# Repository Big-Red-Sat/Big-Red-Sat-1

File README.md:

# Big Red Sat-1

## Introduction 

This repository contains the original designs for the Big Red Sat-1 1U CubeSat, conceived, designed, and launched by a multi-disciplinary team of middle schoolers and high schoolers from the Nebraska public school system, as well as undergraduate students and graduate students from the University of Nebraska-Lincoln.  

The goal of this scientific mission is to characterize the performance and degradation of experimental perovskite solar cells from the National Renewable Energy Laboratory while in low earth orbit.  To accomplish this, a custom precision curve tracer was designed along with a low-Ohm analog multiplexer that was integrated with Near Space Launch's 1U FastBus CubeSat Platform, which incorporates an electrical power system and Iridium satellite communication system for telemetry.  

Electrical connections to the perovskite solar cell samples were made using pogo-pins, with the temperature of each sample being collected with a high-precision temperature sensor affixed to their back face with EP30-2 epoxy.  The enclosure was designed to be airtight to prevent degradation due to humidity and oxygen, so a pressure and humidity sensor were included to monitor changes in this performance.  Since the final samples had a coverslip epoxied to protect the perovskite layer, the airtight property was considered a redundancy.

Big Red Sat-1 was integrated into the Nanoracks CubeSat Deployer 27 (NRCSD27) on 12 December 2023 and launched on 21 March 2024 on the SpaceX CRS-30 mission.   

Big Red Sat-1 was deployed from NRCSD27 by Voyager Space on 18 April 2024 at 18:05:09 UTC ([Deployment Clip](https://www.youtube.com/clip/UgkxD5o3cp39FE0SL8AzyLTBCwdvlqdmNVEa)).  The satellite made first communication with the operations team at 03:00:10 UTC on 19 April 2024.  The satellite deorbited sometime after 23:41:51 UTC on 1 August 2024 after 105 days of operation.

## TLE Data

[Up to date TLE data and visualizations](https://orbit.ing-now.com/satellite/59560/1998-067wk/1998-067wk/)

## Launch Patch

Original concept by Morgan Hurtz, branding by Vince Orsi.

## Current Satellite Location

[SatNOGS DB - Big Red Sat-1](https://db.satnogs.org/satellite/YJQI-7143-2488-2930-9322#mapcontent)

## Prototyping Designs

- [Prototype curve tracers for high altitude balloons](https://github.com/wsarce/Big-Red-Sat-1/tree/main/Prototyping/SIV_pcb)
- [Prototype digital potentiometer curve tracer](https://github.com/wsarce/Big-Red-Sat-1/tree/main/Prototyping/singular_SIV)
- [Prototype resistor ladder curve tracer in LaunchPad form factor](https://github.com/wsarce/Big-Red-Sat-1/tree/main/Prototyping/resistor_ladder_curve_tracer)
- [Prototype analog multiplexer in LaunchPad form factor](https://github.com/wsarce/Big-Red-Sat-1/tree/main/Prototyping/perovskite_switcher/v2)
- [Pressure testing setup with ESP32 and data](https://github.com/wsarce/Big-Red-Sat-1/tree/main/Prototyping/pressure-monitor)
- [Payload breakout board to interact with perovskite cells in payload](https://github.com/wsarce/Big-Red-Sat-1/tree/main/Prototyping/payload-breakout-board/Gecko_Poker)
- [Temperature sensor prototyping](https://github.com/wsarce/Big-Red-Sat-1/tree/main/Prototyping/temp-sensor-prototyping)
- [Neopixel perovskite pixel isolator](https://github.com/wsarce/Big-Red-Sat-1/tree/main/Prototyping/perovskite-cell-isolator)
- [Prototype flight computer with curve tracer and multiplexer](https://github.com/wsarce/Big-Red-Sat-1/tree/main/Prototyping/payload_controller)
- [Magnet mounting jig for orbit alignment magnet](https://github.com/wsarce/Big-Red-Sat-1/tree/main/Prototyping/magnet_mounting)
- [Ossila AM1.5 standoff and mounts](https://github.com/wsarce/Big-Red-Sat-1/tree/main/Prototyping/ossila_mounting)
- [Tooling for building the payload](https://github.com/wsarce/Big-Red-Sat-1/tree/main/Prototyping/payload_mounting)

## Final Designs

- [Flight computer with curve tracer and analog multiplexer](https://github.com/wsarce/Big-Red-Sat-1/tree/main/Flight%20Hardware/flight_computer/v3)
- [Secondary payload with IMU and relay](https://github.com/wsarce/Big-Red-Sat-1/tree/main/Flight%20Hardware/secondary_payload)
- [Tag-Connect programming and data interface](https://github.com/wsarce/Big-Red-Sat-1/tree/main/Flight%20Hardware/Tag%20Connector)
- [Perovskite contact temperature and humiditiy sensor](https://github.com/wsarce/Big-Red-Sat-1/tree/main/Flight%20Hardware/perovskite_contact_board/V7)
- [Perovskite pogo pin board](https://github.com/wsarce/Big-Red-Sat-1/tree/main/Flight%20Hardware/perovskite_contact_board/V6/bot)
- [Perovskite payload enclosure](https://github.com/wsarce/Big-Red-Sat-1/tree/main/Flight%20Payload/Mechanical%20Design)

## Software Developed

- [NSL-EPS-Arduino, an Arduino library to communicate with the NSL electrical power system and radio](https://github.com/wsarce/NSL-EPS-Arduino)
- [FSS100-Arduino, an Arduino library to communicate with the FSS100 sun vector sensor to detect position of sun](https://github.com/wsarce/FSS100-Arduino)
- [pyOssila, a Python library to communicate with the AM1.5 sun simulator](https://github.com/wsarce/pyOssila)
- [Flight firmware for Big Red Sat-1](https://github.com/wsarce/Big-Red-Sat-1/blob/main/Flight%20Hardware/flight_computer/v3/Firmware/brs_flight_firmware/brs_flight_firmware.ino)

## Satellite Exploded View Render

https://github.com/wsarce/Big-Red-Sat-1/assets/22334349/7d4744a6-e3ca-4aac-ab56-a3370dd9aef9

### Contact
For questions, contact either Karen Stelling (kstelling2@unl.edu) or Walker Arce (wsarcera@gmail.com).

### Citation
Arce, W., & Murch-Shafer, J. (2023). Big Red Sat-1 (Version v1.0) [Computer software & hardware]. https://github.com/wsarce/Big-Red-Sat-1

### Funding and Collaboration
This work would not be possible without the generous assistance of our donors and collaborators, listed in alphabetical order below.
1.	Ameritas
2.	Acklie Charitable Foundation
3.	Cooper Foundation
4.	CubeSat Launch Initiative
5.	Ethel S. Abbott Charitable Foundation
6.	Individual Donors
7.	Millard Public Schools Foundation
8.	Monolith
9.	NASA
10.	NASA Nebraska Space Grant
11.	National Renewable Energy Laboratory
12.	Rhodes College
13.	Rodgers Foundation
14.	University of Nebraska-College of Engineering
15.	Oklahoma University

### Media

[April 21, 2021 - NASA selects Nebraska students’ satellite to orbit in space](https://news.unl.edu/newsrooms/today/article/nasa-selects-nebraska-students-satellite-to-orbit-in-space/)

[March 6, 2024 - Big Red Sat Team readies for ISS launch](https://news.unl.edu/newsrooms/today/article/big-red-sat-team-readies-for-iss-launch/)

[March 15, 2024 - Young Nebraska scientists built a satellite, it's now headed to space](https://nebraskapublicmedia.org/en/news/news-articles/young-nebraska-scientists-built-a-satellite-its-now-headed-to-space/)

[March 18, 2024 - NASA Set to Launch Four CubeSats to Space Station](https://blogs.nasa.gov/smallsatellites/2024/03/18/nasa-set-to-launch-four-cubesats-to-space-station/)

[March 21, 2024 - Nebraska students launch satellite into space](https://www.1011now.com/2024/03/21/nebraska-students-launch-satellite-into-space/)

[March 25, 2024 - NASA Space X resupply rocket launches Nebraska CubeSat into outer space](https://engineering.unl.edu/news/240325/nasa_cubesat_launch/)

[March 29, 2024 - Satellite launch a success for Nebraska Engineering team](https://news.unl.edu/newsrooms/today/article/satellite-launch-a-success-for-nebraska-engineering-team/)

[April 22, 2024 - Nebraska's first research satellite reaches International Space Station](https://www.hastingstribune.com/news/nebraskas-first-research-satellite-reaches-international-space-station/article_87f0fb4a-ffdd-11ee-b091-f7073b412070.html)

### Dataset Metadata
The following table is necessary for this dataset to be indexed by search
engines such as <a href="https://g.co/datasetsearch">Google Dataset Search</a>.
<div itemscope itemtype="http://schema.org/Dataset">
<table>
<tr>
<th>property</th>
<th>value</th>
</tr>
<tr>
<td>name</td>
<td><code itemprop="name">Big Red Sat-1 design dataset</code></td>
</tr>
<tr>
<td>description</td>
<td><code itemprop="description">The dataset and designs from the development of the Big Red Sat-1 cube satellite.</code></td>
</tr>
</tr>
<tr>
<td>url</td>
<td><code itemprop="url">https://github.com/wsarce/Big-Red-Sat-1</code></td>
</tr>
<tr>
<td>sameAs</td>
<td><code itemprop="sameAs">https://github.com/wsarce/Big-Red-Sat-1</code></td>
</tr>
<tr>
<td>citation</td>
<td><code itemprop="citation">TBA</code></td>
</tr>
<tr>
<td>hw license</td>
<td>
<div itemscope itemtype="http://schema.org/CreativeWork" itemprop="license">
<table>
<tr>
<th>property</th>
<th>value</th>
</tr>
<tr>
<td>name</td>
<td><code itemprop="name">CERN-OHL-S-2.0</code></td>
</tr>
<tr>
<td>url</td>
<td><code itemprop="url">https://spdx.org/licenses/CERN-OHL-S-2.0.html</code></td>
</tr>
</table>
</div>
</td>
</tr>
<tr>
<td>sw license</td>
<td>
<div itemscope itemtype="http://schema.org/CreativeWork" itemprop="license">
<table>
<tr>
<th>property</th>
<th>value</th>
</tr>
<tr>
<td>name</td>
<td><code itemprop="name">MIT</code></td>
</tr>
<tr>
<td>url</td>
<td><code itemprop="url">https://opensource.org/licenses/MIT</code></td>
</tr>
</table>
</div>
</td>
</tr>
<tr>
<td>docs license</td>
<td>
<div itemscope itemtype="http://schema.org/CreativeWork" itemprop="license">
<table>
<tr>
<th>property</th>
<th>value</th>
</tr>
<tr>
<td>name</td>
<td><code itemprop="name">CC BY-SA 4.0</code></td>
</tr>
<tr>
<td>url</td>
<td><code itemprop="url">https://creativecommons.org/licenses/by-sa/4.0/</code></td>
</tr>
</table>
</div>
</td>
</tr>
</table>
</div>

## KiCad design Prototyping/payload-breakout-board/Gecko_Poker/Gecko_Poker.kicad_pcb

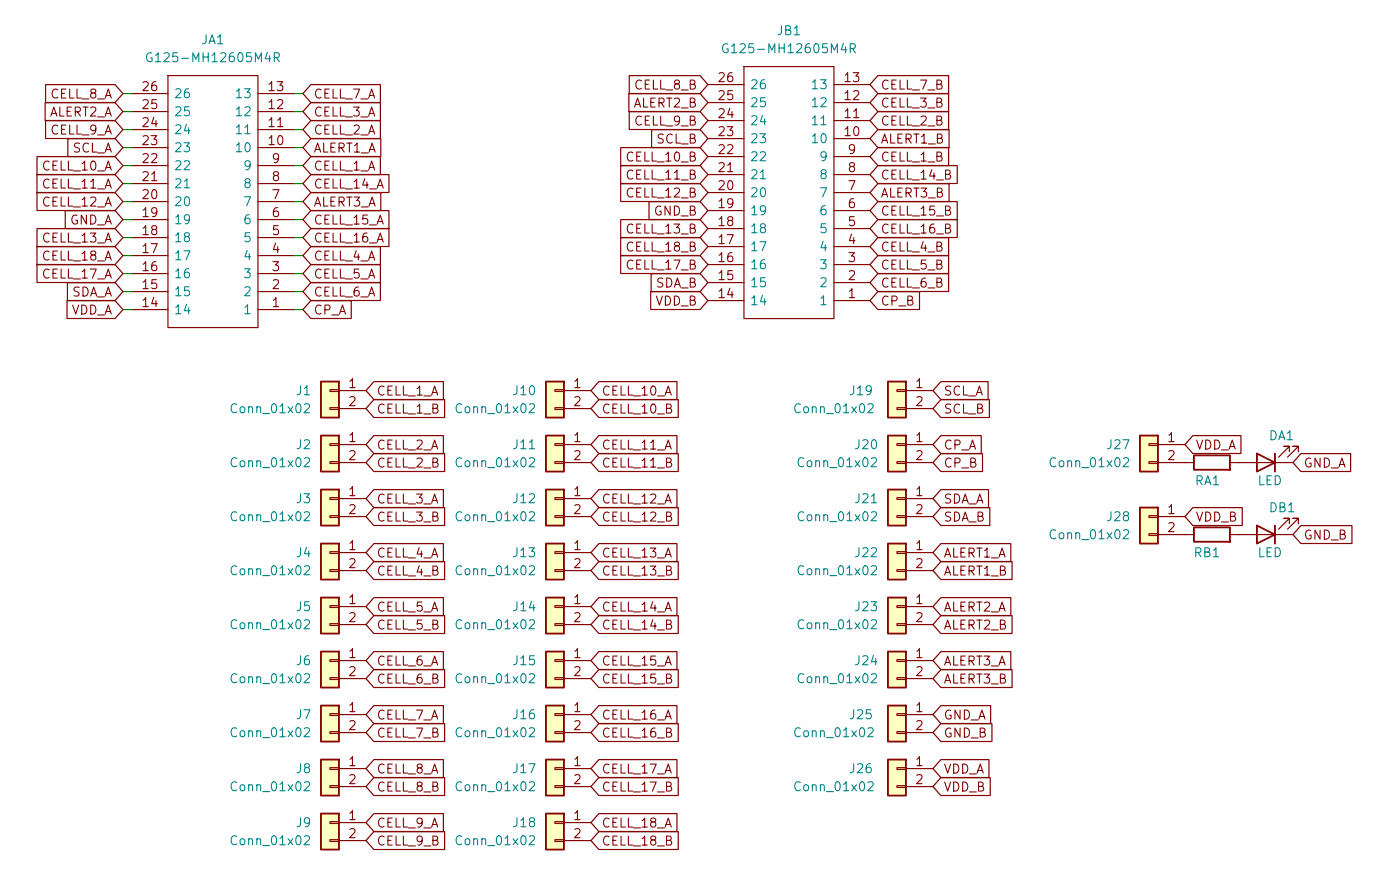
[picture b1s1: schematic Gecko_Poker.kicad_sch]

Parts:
DA1: LED; LED_0805_2012Metric
DB1: LED; LED_0805_2012Metric
J1, J2, J3, J4, J5, J6, J7, J8, J9, J10, J11, J12, J13, J14, J15, J16, J17, J18, J19, J20, J21, J22, J23, J24, J25, J26, J27, J28: Conn_01x02; PinHeader_1x02_P2.54mm_Vertical
JA1: G125-MH12605M4R; G125-MV12605M1P; Manufacturer_Part_Number G125-MH12605M4R; Mouser Part Number 855-G125MH1265M4RM4R
JB1: G125-MH12605M4R; G125-MV12605M1P; Manufacturer_Part_Number G125-MH12605M4R; Mouser Part Number 855-G125MH1265M4RM4R
RA1: (no value)
RB1: (no value)

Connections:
ALERT1_A: J22.1, JA1.10
ALERT1_B: J22.2, JB1.10
ALERT2_A: J23.1, JA1.25
ALERT2_B: J23.2, JB1.25
ALERT3_A: J24.1, JA1.7
ALERT3_B: J24.2, JB1.7
CELL_1_A: J1.1, JA1.9
CELL_1_B: J1.2, JB1.9
CELL_2_A: J2.1, JA1.11
CELL_2_B: J2.2, JB1.11
CELL_3_A: J3.1, JA1.12
CELL_3_B: J3.2, JB1.12
CELL_4_A: J4.1, JA1.4
CELL_4_B: J4.2, JB1.4
CELL_5_A: J5.1, JA1.3
CELL_5_B: J5.2, JB1.3
CELL_6_A: J6.1, JA1.2
CELL_6_B: J6.2, JB1.2
CELL_7_A: J7.1, JA1.13
CELL_7_B: J7.2, JB1.13
CELL_8_A: J8.1, JA1.26
CELL_8_B: J8.2, JB1.26
CELL_9_A: J9.1, JA1.24
CELL_9_B: J9.2, JB1.24
CELL_10_A: J10.1, JA1.22
CELL_10_B: J10.2, JB1.22
CELL_11_A: J11.1, JA1.21
CELL_11_B: J11.2, JB1.21
CELL_12_A: J12.1, JA1.20
CELL_12_B: J12.2, JB1.20
CELL_13_A: J13.1, JA1.18
CELL_13_B: J13.2, JB1.18
CELL_14_A: J14.1, JA1.8
CELL_14_B: J14.2, JB1.8
CELL_15_A: J15.1, JA1.6
CELL_15_B: J15.2, JB1.6
CELL_16_A: J16.1, JA1.5
CELL_16_B: J16.2, JB1.5
CELL_17_A: J17.1, JA1.16
CELL_17_B: J17.2, JB1.16
CELL_18_A: J18.1, JA1.17
CELL_18_B: J18.2, JB1.17
CP_A: J20.1, JA1.1
CP_B: J20.2, JB1.1
GND_A: DA1.1 (K), J25.1, JA1.19
GND_B: DB1.1 (K), J25.2, JB1.19
unnamed: DA1.2 (A), RA1.2
unnamed: DB1.2 (A), RB1.2
unnamed: J27.2, RA1.1
unnamed: J28.2, RB1.1
SCL_A: J19.1, JA1.23
SCL_B: J19.2, JB1.23
SDA_A: J21.1, JA1.15
SDA_B: J21.2, JB1.15
VDD_A: J26.1, J27.1, JA1.14
VDD_B: J26.2, J28.1, JB1.14

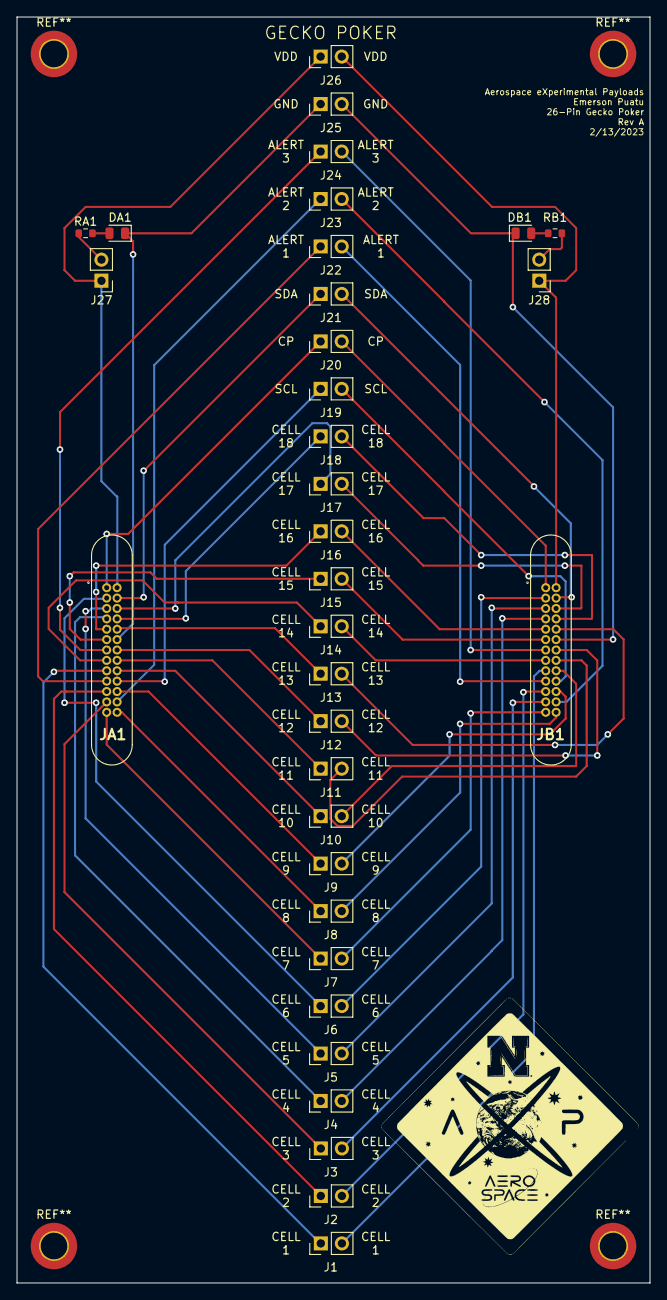
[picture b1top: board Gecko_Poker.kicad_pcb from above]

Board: 2 copper layers, 76.2 x 152.4 mm, 34 parts (0 on the bottom side), 56 nets.

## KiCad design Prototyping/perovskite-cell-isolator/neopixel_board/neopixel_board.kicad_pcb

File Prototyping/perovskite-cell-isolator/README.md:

# Perovskite Cell Isolator

 * Use NeoPixel Mini 3535 
 * Part is included in KiCAD

## Getting started

To make it easy for you to get started with GitLab, here's a list of recommended next steps.

Already a pro? Just edit this README.md and make it your own. Want to make it easy? [Use the template at the bottom](#editing-this-readme)!

## Add your files

- [ ] [Create](https://docs.gitlab.com/ee/user/project/repository/web_editor.html#create-a-file) or [upload](https://docs.gitlab.com/ee/user/project/repository/web_editor.html#upload-a-file) files
- [ ] [Add files using the command line](https://docs.gitlab.com/ee/gitlab-basics/add-file.html#add-a-file-using-the-command-line) or push an existing Git repository with the following command:

```
cd existing_repo
git remote add origin https://git.unl.edu/unl-axp/perovskite-cell-isolator.git
git branch -M main
git push -uf origin main
```

## Integrate with your tools

- [ ] [Set up project integrations](https://git.unl.edu/unl-axp/perovskite-cell-isolator/-/settings/integrations)

## Collaborate with your team

- [ ] [Invite team members and collaborators](https://docs.gitlab.com/ee/user/project/members/)
- [ ] [Create a new merge request](https://docs.gitlab.com/ee/user/project/merge_requests/creating_merge_requests.html)
- [ ] [Automatically close issues from merge requests](https://docs.gitlab.com/ee/user/project/issues/managing_issues.html#closing-issues-automatically)
- [ ] [Enable merge request approvals](https://docs.gitlab.com/ee/user/project/merge_requests/approvals/)
- [ ] [Automatically merge when pipeline succeeds](https://docs.gitlab.com/ee/user/project/merge_requests/merge_when_pipeline_succeeds.html)

## Test and Deploy

Use the built-in continuous integration in GitLab.

- [ ] [Get started with GitLab CI/CD](https://docs.gitlab.com/ee/ci/quick_start/index.html)
- [ ] [Analyze your code for known vulnerabilities with Static Application Security Testing(SAST)](https://docs.gitlab.com/ee/user/application_security/sast/)
- [ ] [Deploy to Kubernetes, Amazon EC2, or Amazon ECS using Auto Deploy](https://docs.gitlab.com/ee/topics/autodevops/requirements.html)
- [ ] [Use pull-based deployments for improved Kubernetes management](https://docs.gitlab.com/ee/user/clusters/agent/)
- [ ] [Set up protected environments](https://docs.gitlab.com/ee/ci/environments/protected_environments.html)

***

# Editing this README

When you're ready to make this README your own, just edit this file and use the handy template below (or feel free to structure it however you want - this is just a starting point!). Thank you to [makeareadme.com](https://www.makeareadme.com/) for this template.

## Suggestions for a good README
Every project is different, so consider which of these sections apply to yours. The sections used in the template are suggestions for most open source projects. Also keep in mind that while a README can be too long and detailed, too long is better than too short. If you think your README is too long, consider utilizing another form of documentation rather than cutting out information.

## Name
Choose a self-explaining name for your project.

## Description
Let people know what your project can do specifically. Provide context and add a link to any reference visitors might be unfamiliar with. A list of Features or a Background subsection can also be added here. If there are alternatives to your project, this is a good place to list differentiating factors.

## Badges
On some READMEs, you may see small images that convey metadata, such as whether or not all the tests are passing for the project. You can use Shields to add some to your README. Many services also have instructions for adding a badge.

## Visuals
Depending on what you are making, it can be a good idea to include screenshots or even a video (you'll frequently see GIFs rather than actual videos). Tools like ttygif can help, but check out Asciinema for a more sophisticated method.

## Installation
Within a particular ecosystem, there may be a common way of installing things, such as using Yarn, NuGet, or Homebrew. However, consider the possibility that whoever is reading your README is a novice and would like more guidance. Listing specific steps helps remove ambiguity and gets people to using your project as quickly as possible. If it only runs in a specific context like a particular programming language version or operating system or has dependencies that have to be installed manually, also add a Requirements subsection.

## Usage
Use examples liberally, and show the expected output if you can. It's helpful to have inline the smallest example of usage that you can demonstrate, while providing links to more sophisticated examples if they are too long to reasonably include in the README.

## Support
Tell people where they can go to for help. It can be any combination of an issue tracker, a chat room, an email address, etc.

## Roadmap
If you have ideas for releases in the future, it is a good idea to list them in the README.

## Contributing
State if you are open to contributions and what your requirements are for accepting them.

For people who want to make changes to your project, it's helpful to have some documentation on how to get started. Perhaps there is a script that they should run or some environment variables that they need to set. Make these steps explicit. These instructions could also be useful to your future self.

You can also document commands to lint the code or run tests. These steps help to ensure high code quality and reduce the likelihood that the changes inadvertently break something. Having instructions for running tests is especially helpful if it requires external setup, such as starting a Selenium server for testing in a browser.

## Authors and acknowledgment
Show your appreciation to those who have contributed to the project.

## License
For open source projects, say how it is licensed.

## Project status
If you have run out of energy or time for your project, put a note at the top of the README saying that development has slowed down or stopped completely. Someone may choose to fork your project or volunteer to step in as a maintainer or owner, allowing your project to keep going. You can also make an explicit request for maintainers.
All I am is a radio googoo
i love emerson

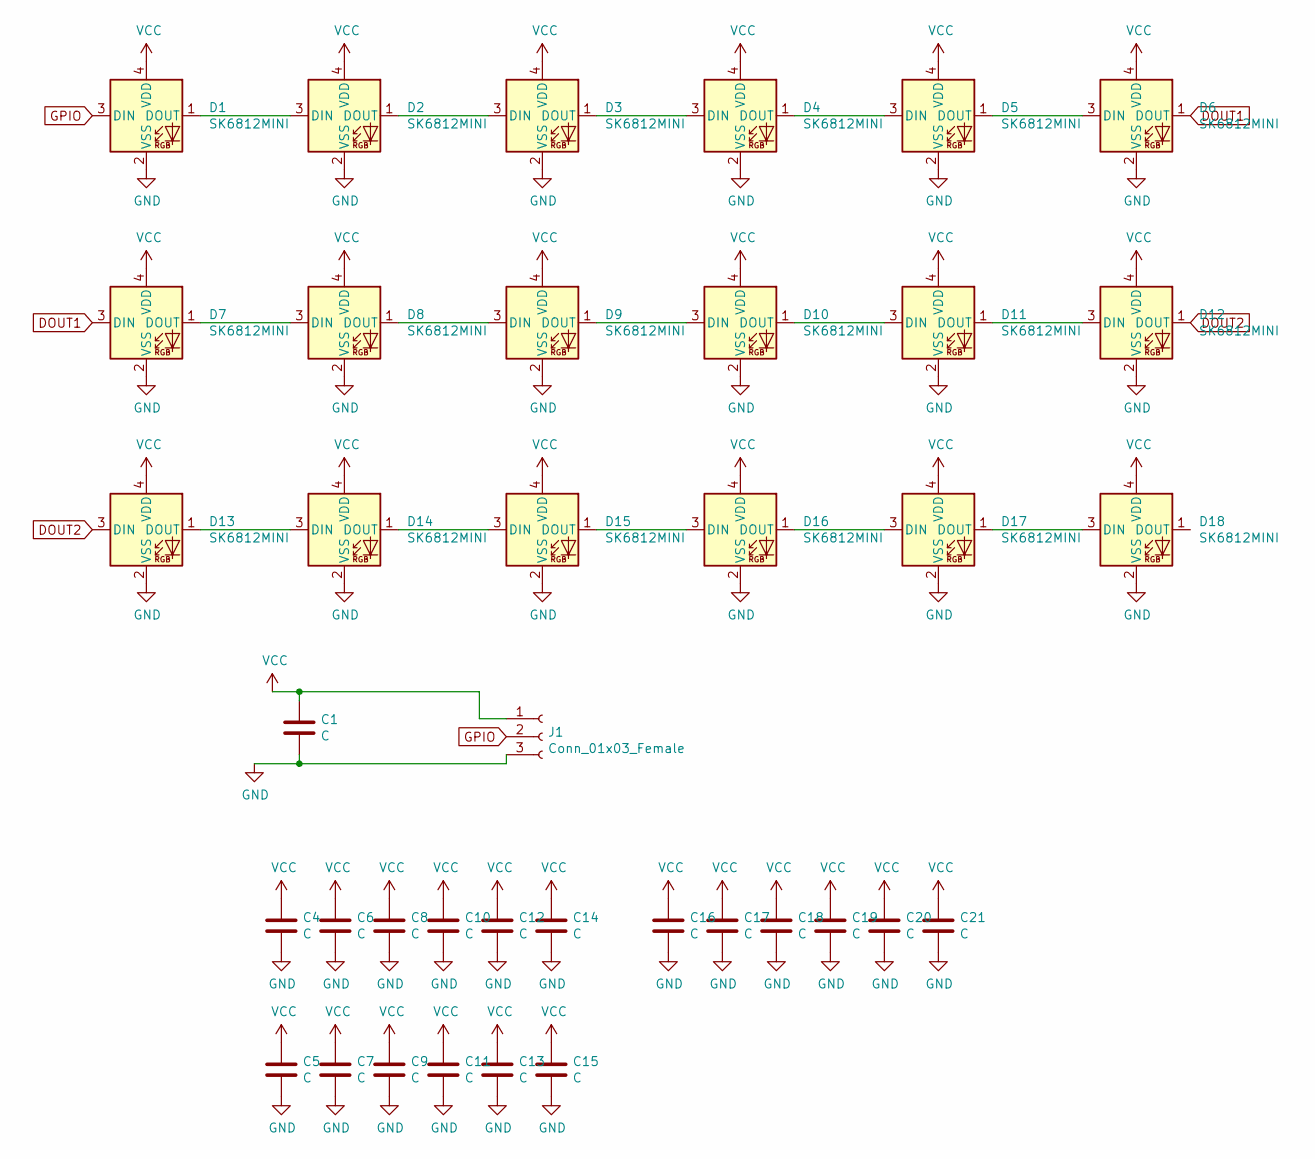
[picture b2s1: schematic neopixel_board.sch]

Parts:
C1: C; CP_Radial_D10.0mm_P5.00mm
C4, C5, C6, C7, C8, C9, C10, C11, C12, C13, C14, C15, C16, C17, C18, C19, C20, C21: C; C_0805_2012Metric
D1, D2, D3, D4, D5, D6, D7, D8, D9, D10, D11, D12, D13, D14, D15, D16, D17, D18: SK6812MINI; LED_SK6812MINI_PLCC4_3.5x3.5mm_P1.75mm
J1: Conn_01x03_Female; PinHeader_1x03_P2.54mm_Vertical

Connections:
DOUT1: D6.1 (DOUT), D7.3 (DIN)
DOUT2: D12.1 (DOUT), D13.3 (DIN)
GND: C1.2, C4.2, C5.2, C6.2, C7.2, C8.2, C9.2, C10.2, C11.2, C12.2, C13.2, C14.2, C15.2, C16.2, C17.2, C18.2, C19.2, C20.2, C21.2, D1.2 (VSS), D2.2 (VSS), D3.2 (VSS), D4.2 (VSS), D5.2 (VSS), D6.2 (VSS), D7.2 (VSS), D8.2 (VSS), D9.2 (VSS), D10.2 (VSS), D11.2 (VSS), D12.2 (VSS), D13.2 (VSS), D14.2 (VSS), D15.2 (VSS), D16.2 (VSS), D17.2 (VSS), D18.2 (VSS), J1.3; also elsewhere on the board
GPIO: D1.3 (DIN), J1.2
unnamed: D1.1 (DOUT), D2.3 (DIN)
unnamed: D2.1 (DOUT), D3.3 (DIN)
unnamed: D3.1 (DOUT), D4.3 (DIN)
unnamed: D4.1 (DOUT), D5.3 (DIN)
unnamed: D5.1 (DOUT), D6.3 (DIN)
unnamed: D7.1 (DOUT), D8.3 (DIN)
unnamed: D8.1 (DOUT), D9.3 (DIN)
unnamed: D10.1 (DOUT), D11.3 (DIN)
unnamed: D9.1 (DOUT), D10.3 (DIN)
unnamed: D11.1 (DOUT), D12.3 (DIN)
unnamed: D13.1 (DOUT), D14.3 (DIN)
unnamed: D14.1 (DOUT), D15.3 (DIN)
unnamed: D15.1 (DOUT), D16.3 (DIN)
unnamed: D16.1 (DOUT), D17.3 (DIN)
unnamed: D17.1 (DOUT), D18.3 (DIN)
VCC: C1.1, C4.1, C5.1, C6.1, C7.1, C8.1, C9.1, C10.1, C11.1, C12.1, C13.1, C14.1, C15.1, C16.1, C17.1, C18.1, C19.1, C20.1, C21.1, D1.4 (VDD), D2.4 (VDD), D3.4 (VDD), D4.4 (VDD), D5.4 (VDD), D6.4 (VDD), D7.4 (VDD), D8.4 (VDD), D9.4 (VDD), D10.4 (VDD), D11.4 (VDD), D12.4 (VDD), D13.4 (VDD), D14.4 (VDD), D15.4 (VDD), D16.4 (VDD), D17.4 (VDD), D18.4 (VDD), J1.1; also elsewhere on the board

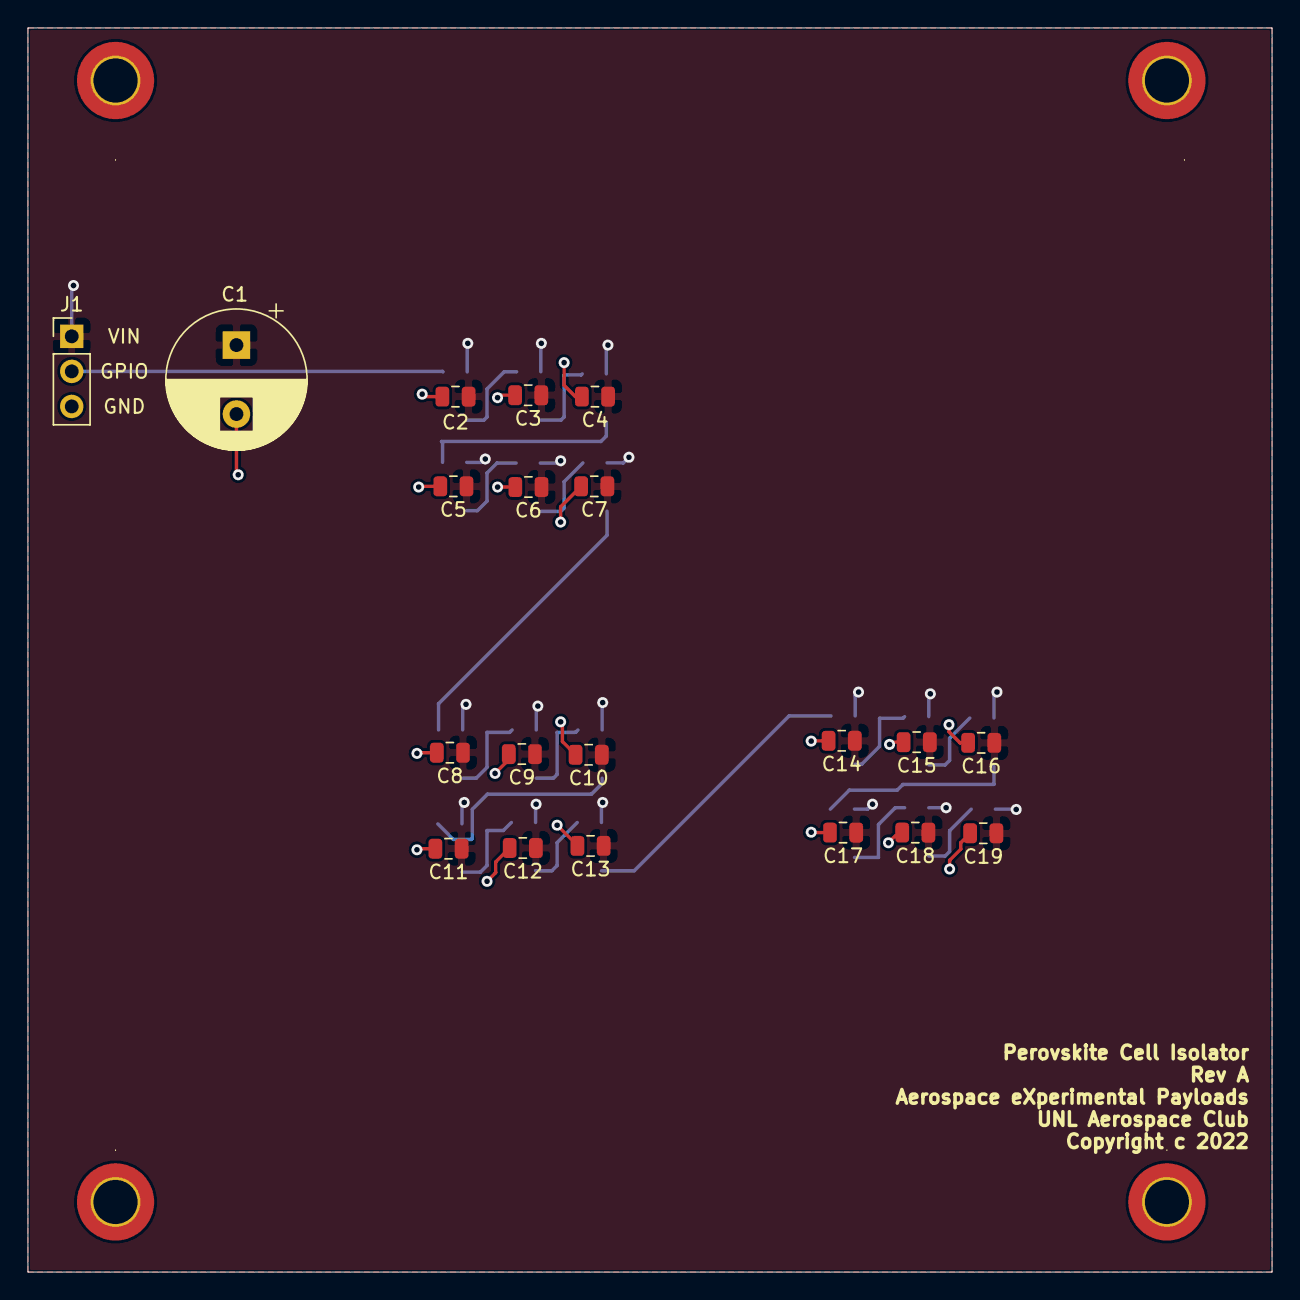
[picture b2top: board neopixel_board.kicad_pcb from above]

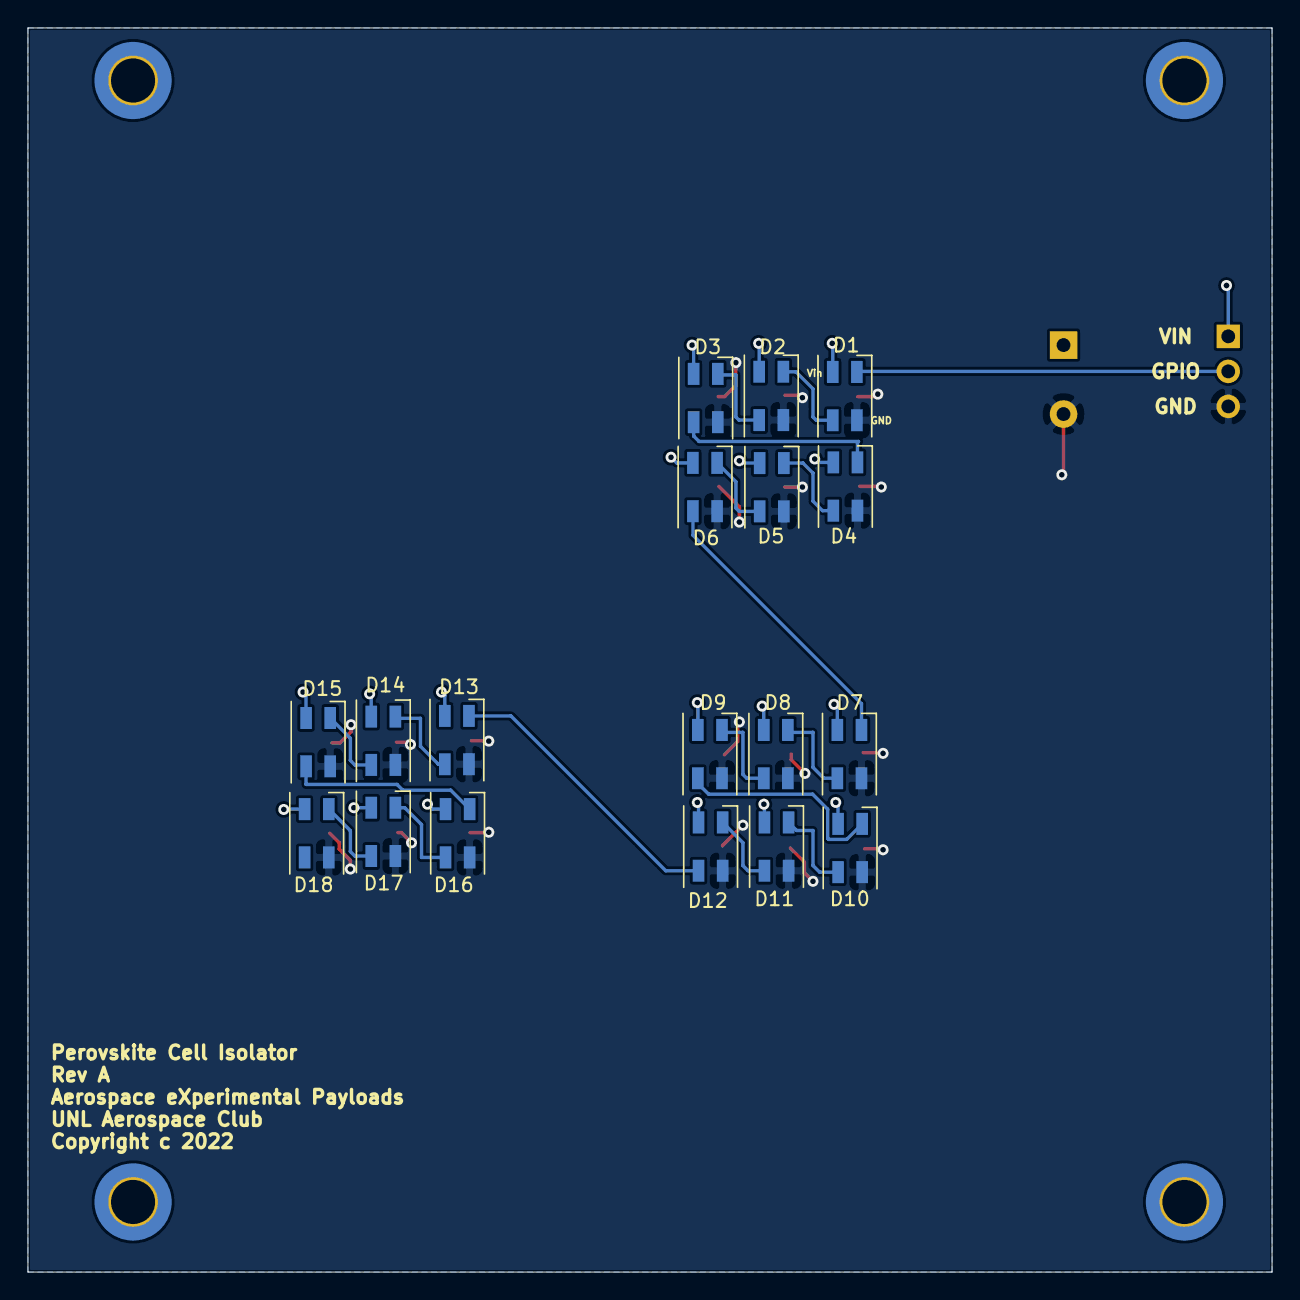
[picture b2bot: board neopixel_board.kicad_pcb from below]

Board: 2 copper layers, 90.2 x 90.2 mm, 42 parts (18 on the bottom side), 20 nets.

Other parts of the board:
., .#2, .#3, .#4: MountingHole_3.2mm_M3_DIN965_Pad_TopBottom
C2, C3: C; C_0805_2012Metric

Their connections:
GND: C2.2, C3.2; also elsewhere on the board
VCC: C2.1, C3.1; also elsewhere on the board

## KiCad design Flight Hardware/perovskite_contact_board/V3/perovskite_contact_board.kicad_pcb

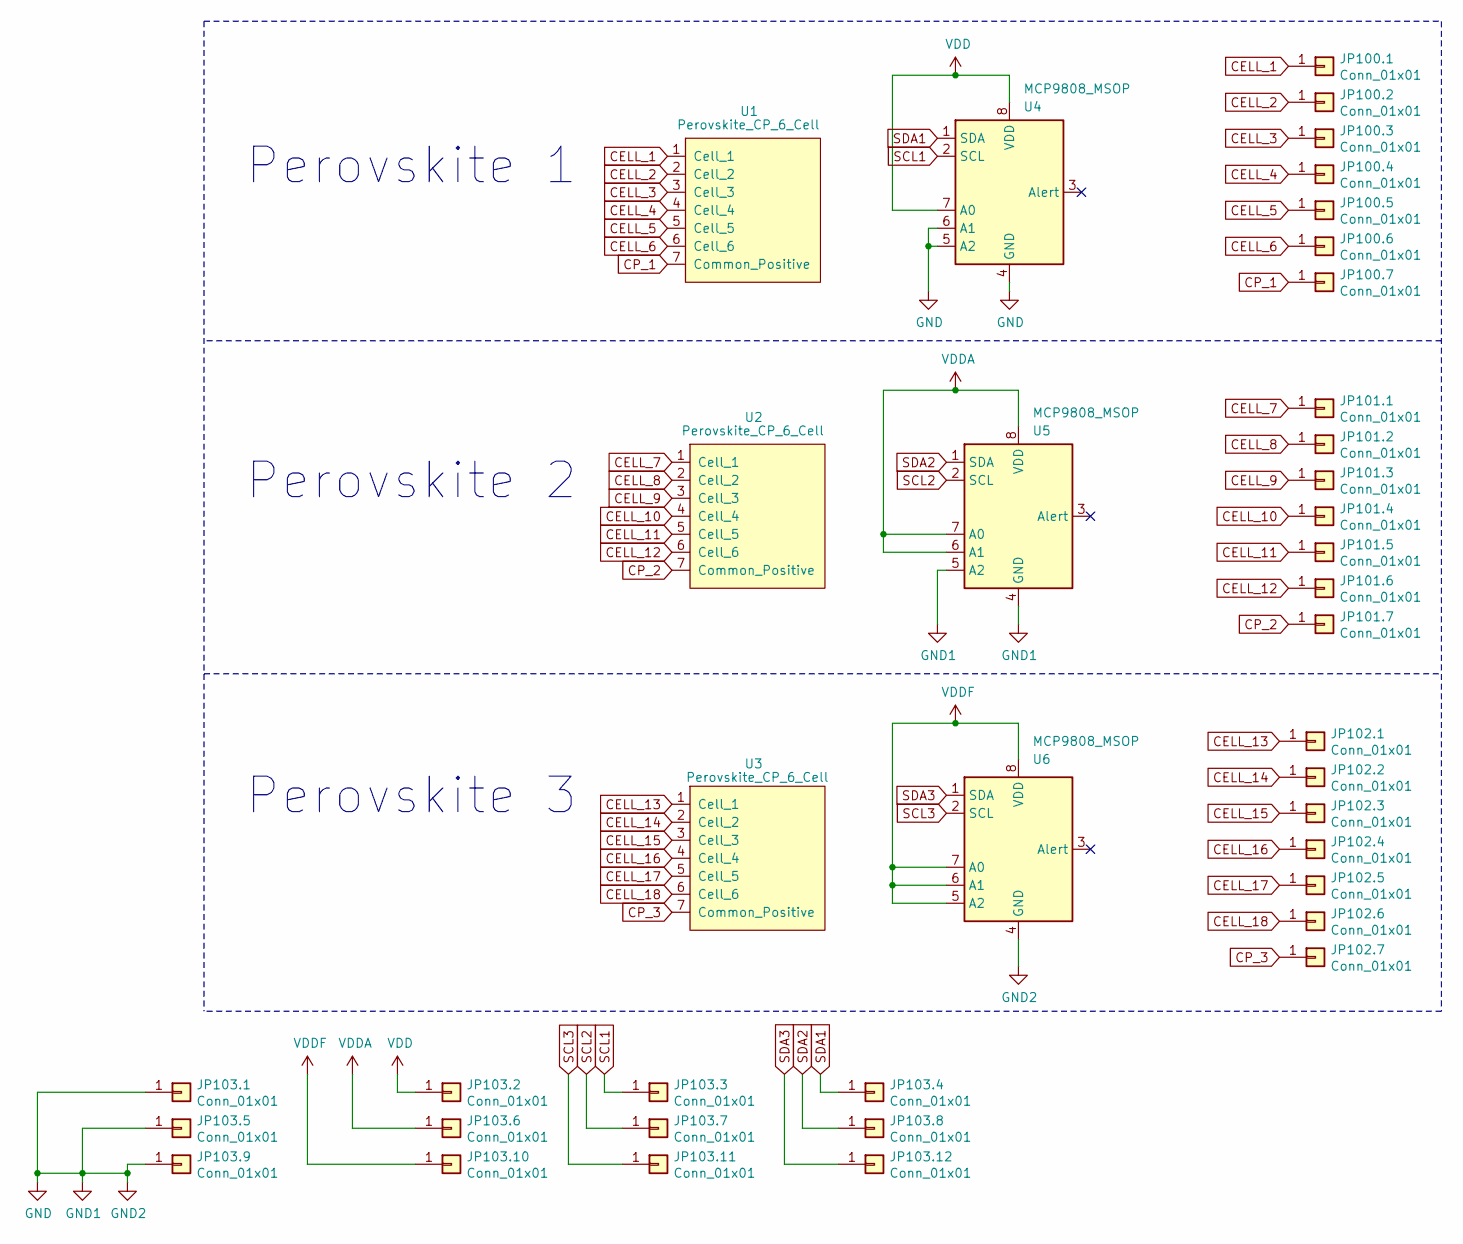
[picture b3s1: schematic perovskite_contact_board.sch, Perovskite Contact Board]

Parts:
JP100.1, JP100.2, JP100.3, JP100.4, JP100.5, JP100.6, JP100.7, JP101.1, JP101.2, JP101.3, JP101.4, JP101.5, JP101.6, JP101.7, JP102.1, JP102.2, JP102.3, JP102.4, JP102.5, JP102.6, JP102.7, JP103.1, JP103.2, JP103.3, JP103.4, JP103.5, JP103.6, JP103.7, JP103.8, JP103.9, JP103.10, JP103.11, JP103.12: Conn_01x01; TestPoint_Pad_D2.0mm
U1, U2, U3: Perovskite_CP_6_Cell; Perovskite
U4, U5, U6: MCP9808_MSOP; MCP9804_With_Hole

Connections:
CELL_1: JP100.1.1, U1.1 (Cell_1)
CELL_2: JP100.2.1, U1.2 (Cell_2)
CELL_3: JP100.3.1, U1.3 (Cell_3)
CELL_4: JP100.4.1, U1.4 (Cell_4)
CELL_5: JP100.5.1, U1.5 (Cell_5)
CELL_6: JP100.6.1, U1.6 (Cell_6)
CELL_7: JP101.1.1, U2.1 (Cell_1)
CELL_8: JP101.2.1, U2.2 (Cell_2)
CELL_9: JP101.3.1, U2.3 (Cell_3)
CELL_10: JP101.4.1, U2.4 (Cell_4)
CELL_11: JP101.5.1, U2.5 (Cell_5)
CELL_12: JP101.6.1, U2.6 (Cell_6)
CELL_13: JP102.1.1, U3.1 (Cell_1)
CELL_14: JP102.2.1, U3.2 (Cell_2)
CELL_15: JP102.3.1, U3.3 (Cell_3)
CELL_16: JP102.4.1, U3.4 (Cell_4)
CELL_17: JP102.5.1, U3.5 (Cell_5)
CELL_18: JP102.6.1, U3.6 (Cell_6)
CP_1: JP100.7.1, U1.7 (Common_Positive)
CP_2: JP101.7.1, U2.7 (Common_Positive)
CP_3: JP102.7.1, U3.7 (Common_Positive)
GND: JP103.1.1, JP103.5.1, JP103.9.1, U4.4 (GND), U4.5 (A2), U4.6 (A1), U5.4 (GND), U5.5 (A2), U6.4 (GND)
SCL1: JP103.3.1, U4.2 (SCL)
SCL2: JP103.7.1, U5.2 (SCL)
SCL3: JP103.11.1, U6.2 (SCL)
SDA1: JP103.4.1, U4.1 (SDA)
SDA2: JP103.8.1, U5.1 (SDA)
SDA3: JP103.12.1, U6.1 (SDA)
VDD: JP103.2.1, U4.7 (A0), U4.8 (VDD)
VDDA: JP103.6.1, U5.6 (A1), U5.7 (A0), U5.8 (VDD)
VDDF: JP103.10.1, U6.5 (A2), U6.6 (A1), U6.7 (A0), U6.8 (VDD)

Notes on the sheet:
Perovskite 1
Perovskite 2
Perovskite 3

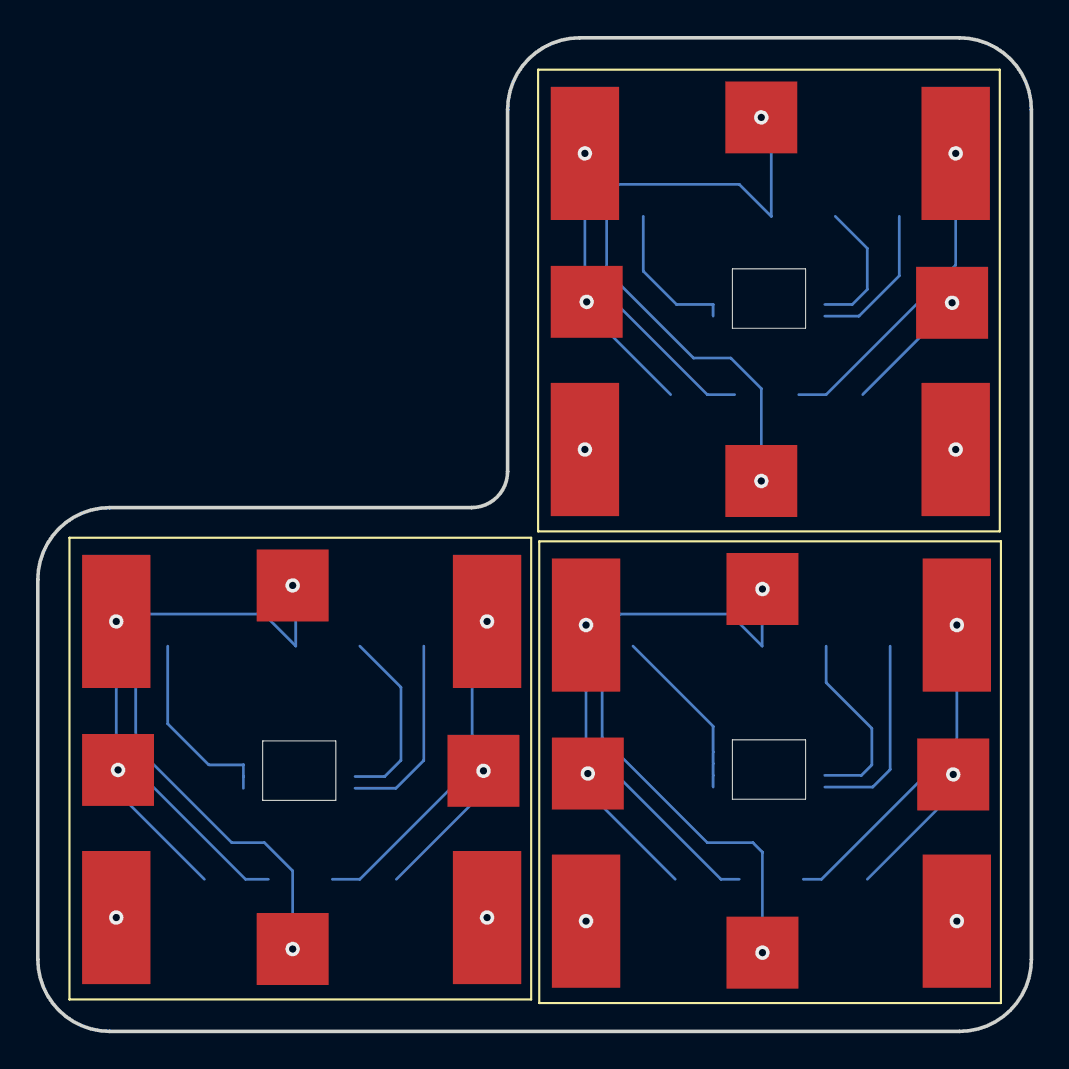
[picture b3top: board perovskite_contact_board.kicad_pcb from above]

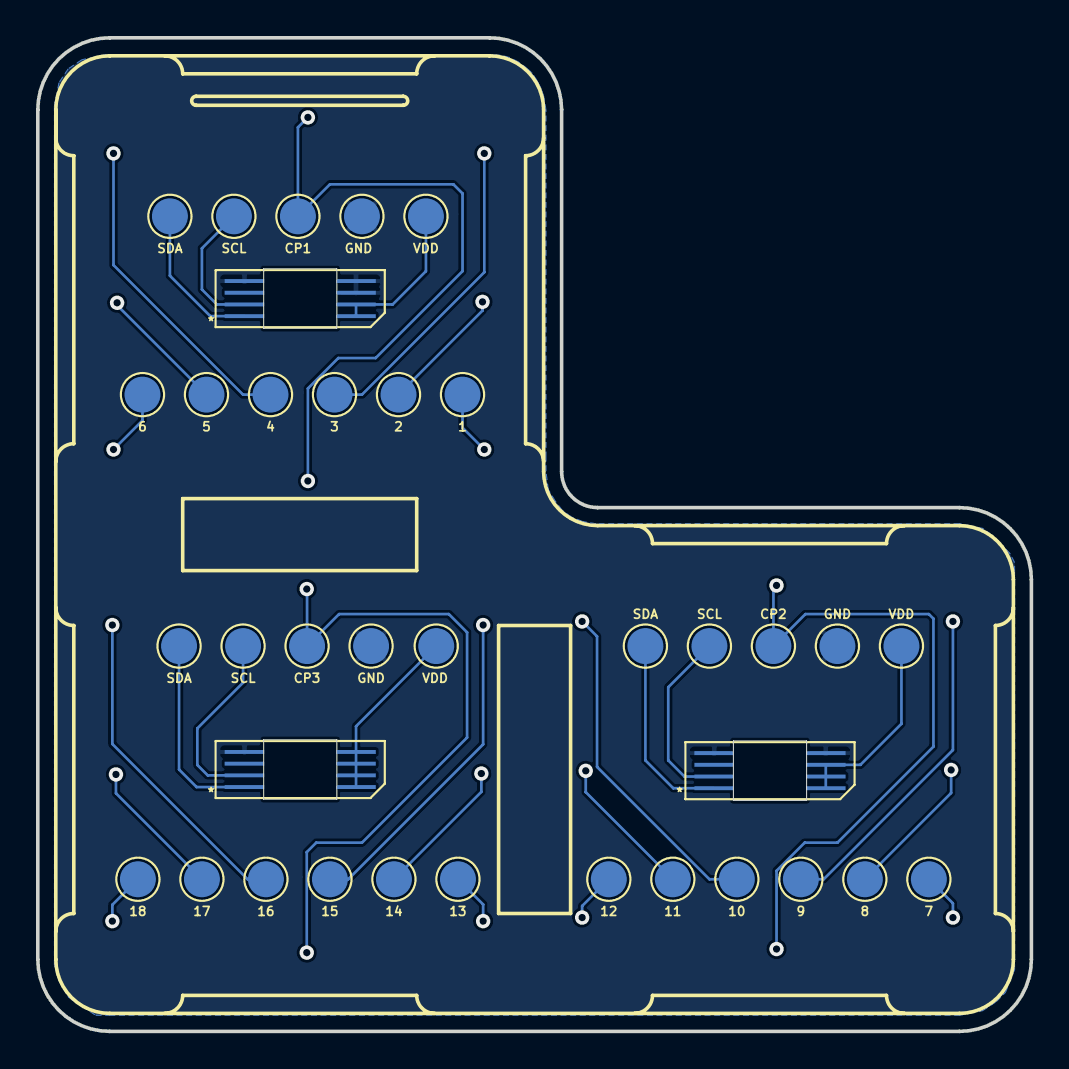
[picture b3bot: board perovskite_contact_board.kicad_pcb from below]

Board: 2 copper layers, 55.2 x 55.2 mm, 39 parts (36 on the bottom side), 31 nets.

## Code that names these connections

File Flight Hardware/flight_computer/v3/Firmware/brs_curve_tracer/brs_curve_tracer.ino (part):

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
void enable_magnetometer_int(void)
{
  attachInterrupt(digitalPinToInterrupt(MAG_INT), handle_secondary_payload_sensors, RISING);
}

void init_imu(void)
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
void init_pins(void)
{
  pinMode(NC_V, INPUT);
  pinMode(S1_CT, OUTPUT);
  digitalWrite(S1_CT, LOW);

  pinMode(READ_CURRENT, INPUT);
  pinMode(READ_VOLTAGE, INPUT);
  pinMode(NO_V, INPUT);
  pinMode(UNSET, OUTPUT);
  digitalWrite(UNSET, LOW);
  pinMode(SET, OUTPUT);
  digitalWrite(SET, LOW);
  pinMode(MAG_INT, INPUT);
  pinMode(CT_GOOD, INPUT);
  pinMode(GAAS_ON, INPUT_PULLUP);

  pinMode(MUX_GOOD, INPUT);
  pinMode(MUX_CLOCK, OUTPUT);
  pinMode(MUX_RESET, OUTPUT);
  digitalWrite(MUX_RESET, LOW);

  pinMode(READ_BUSS, INPUT);

  pinMode(LADDER_CLOCK, OUTPUT);
  digitalWrite(LADDER_CLOCK, HIGH);
  pinMode(TRACE_DIR, OUTPUT);
  digitalWrite(TRACE_DIR, COUNT_UP);

  //  pinMode(GAAS_TEMP, INPUT);
  pinMode(BUSY, INPUT);
  pinMode(PANEL_3_ON, INPUT_PULLUP);
  pinMode(PANEL_3_CURRENT_V, INPUT);

  pinMode(S0_CT, OUTPUT);
  digitalWrite(S0_CT, LOW);

  Wire.begin();
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
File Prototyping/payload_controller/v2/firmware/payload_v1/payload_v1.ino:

/*
 * Payload Controller Firmware
 * UNL Aerospace Club
 * Aerospace eXperimental Payloads
 * 
 * Author: Walker Arce
 * Date: 26 Dec 2022
 */
#include "ADS131M04.h"
#include <MCP9808.h>      // http://github.com/JChristensen/MCP9808
#include "MCP4725.h"
#include <OneWire.h> 

// ADC Pins
#define ADC_CS    11
#define ADC_DRDY  18
#define ADC_MOSI  15
#define ADC_MISO  14
#define ADC_SCLK  7
#define ADC_SYNC  6

// Perovskite Multiplexer Pins
#define ENABLE_TEST_SOURCE    2
#define RESET_PANEL_SWITCH    27
#define ENABLE_PANEL_SWITCH   22
#define DECODER_10_19_CLOCK   21
#define DECODER_0_9_CLOCK     25

// Resistor Ladder Pins
#define R_DIVIDER_CLOCK   12
#define R_DIVIDER_LATCH   28
#define R_DIVIDER_RESET   13
#define R_DIVIDER_ENABLE  19

// GaAs Panel Pins
#define GAAS_TEMP A9

// Other Pins
#define FAULT         8
#define REVERSE_BIAS  26
#define ALERT         23

// Process Control Variables
#define ANALOG_SAMPLES_V      5
#define ANALOG_SAMPLES_I      5
#define DAC_ADDRESS           0x66
#define PEROVSKITE_1_LOWER    1
#define PEROVSKITE_2_LOWER    3 
#define PEROVSKITE_3_LOWER    7
#define FSS100_ADDRESS        0x57

ADS131M04 adc;
adcOutput res;

MCP9808 perovskite_1(PEROVSKITE_1_LOWER);
MCP9808 perovskite_2(PEROVSKITE_2_LOWER);
MCP9808 perovskite_3(PEROVSKITE_3_LOWER);

MCP4725 dac(DAC_ADDRESS); 

//OneWire ds(GAAS_TEMP);

volatile int current_panel = 0;
volatile int current_step = 0;

int v_readings[256];
int i_readings[256];

void setup_pins(void)
{
  pinMode(ENABLE_TEST_SOURCE, OUTPUT);
  digitalWrite(ENABLE_TEST_SOURCE, LOW);
  
  pinMode(RESET_PANEL_SWITCH, OUTPUT);
  digitalWrite(RESET_PANEL_SWITCH, LOW);
  
  pinMode(ENABLE_PANEL_SWITCH, OUTPUT);
  digitalWrite(ENABLE_PANEL_SWITCH, LOW);
  
  pinMode(DECODER_10_19_CLOCK, OUTPUT);
  digitalWrite(DECODER_10_19_CLOCK, LOW);
  
  pinMode(DECODER_0_9_CLOCK, OUTPUT);
  digitalWrite(DECODER_0_9_CLOCK, LOW);

  pinMode(R_DIVIDER_CLOCK, OUTPUT);
  digitalWrite(R_DIVIDER_CLOCK, LOW);
  
  pinMode(R_DIVIDER_LATCH, OUTPUT);
  digitalWrite(R_DIVIDER_LATCH, HIGH);
  
  pinMode(R_DIVIDER_RESET, OUTPUT);
  pinMode(R_DIVIDER_RESET, HIGH);
  
  pinMode(R_DIVIDER_ENABLE, OUTPUT);
  digitalWrite(R_DIVIDER_ENABLE, LOW);

  pinMode(FAULT, OUTPUT);
  digitalWrite(FAULT, LOW);

  pinMode(REVERSE_BIAS, OUTPUT);
  digitalWrite(REVERSE_BIAS, LOW);

  pinMode(ALERT, INPUT);
  pinMode(ADC_SYNC, INPUT);

  Wire.begin();

  adc.begin(ADC_SCLK, ADC_MISO, ADC_MOSI, ADC_CS, ADC_DRDY);
  if (!adc.setInputChannelSelection(0, INPUT_CHANNEL_MUX_AIN0P_AIN0N))
  {
    Serial.println("Could not connect ADC Input 1");
  }
  if (!adc.setInputChannelSelection(3, INPUT_CHANNEL_MUX_AIN0P_AIN0N))
  {
    Serial.println("Could not connect ADC Input 4");
  }
  if (perovskite_1.begin() != 0)
  {
    Serial.println("Could not find perovskite temp sensor 1");
  }
  if (perovskite_2.begin() != 0)
  {
    Serial.println("Could not find perovskite temp sensor 2");
  }
  if (perovskite_3.begin() != 0)
  {
    Serial.println("Could not find perovskite temp sensor 3");
  }
  if (dac.begin() == false)
  {
    Serial.println("Could not find DAC");
  }
}

void read_point(int reading_index)
{
  Serial.print(current_step);
  Serial.print(" ");
  Serial.print(v_readings[reading_index]);
  Serial.print(" ");
  Serial.print(i_readings[reading_index]);
  Serial.println();
}

void reset_ladder(void)
{
  digitalWrite(R_DIVIDER_RESET, LOW);
  digitalWrite(R_DIVIDER_RESET, HIGH);
  current_step = 0;
}

void step_ladder(void)
{
  digitalWrite(R_DIVIDER_CLOCK, HIGH);
  digitalWrite(R_DIVIDER_LATCH, LOW);
  digitalWrite(R_DIVIDER_CLOCK, LOW);
  digitalWrite(R_DIVIDER_LATCH, HIGH);
  current_step++;
}

void trace_curve(void)
{
  for (int i = 0; i < 256; i++)
  {
    while (!adc.isDataReady());
    res = adc.readADC();
    
    v_readings[i] = res.ch3;
    i_readings[i] = res.ch0;
    
    step_ladder();
  }
  for (int i = 0; i < 256; i++)
  {
    read_point(i);
  }
  reset_ladder();
}

void step_decoder(void)
{
  if (current_panel == 11)
  {
    digitalWrite(ENABLE_PANEL_SWITCH, HIGH);
  }
  if (current_panel > 10)
  {
    digitalWrite(DECODER_10_19_CLOCK, HIGH);
    digitalWrite(DECODER_10_19_CLOCK, LOW);
  }
  else
  {
    digitalWrite(DECODER_0_9_CLOCK, HIGH);
    digitalWrite(DECODER_0_9_CLOCK, LOW);
  }
  current_panel++;
  if (current_panel > 20)
  {
    reset_decoder();
  }
  Serial.println(current_panel);
}

void reset_decoder(void)
{
  current_panel = 1;
  digitalWrite(RESET_PANEL_SWITCH, HIGH);
  digitalWrite(RESET_PANEL_SWITCH, LOW);
  
  digitalWrite(ENABLE_PANEL_SWITCH, LOW);
  digitalWrite(DECODER_0_9_CLOCK, LOW);
  digitalWrite(DECODER_10_19_CLOCK, LOW);
}

void setup() {
  Serial.begin(115200);
  Serial.println("Payload V1 starting up");
  setup_pins();
  reset_decoder();
  reset_ladder();
}

uint16_t output_v = 2000;
void loop() {
  while (true)
  {
    Serial.print(dac.setValue(output_v++));
    Serial.print(": ");
    Serial.println(output_v);
    delay(100);
    if (output_v > 4095) output_v = 0;
  }
  while (Serial.available() > 0)
  {
    char command[1];
    char params[1];
    size_t bytesRead = Serial.readBytes(command, 1);
    if (command[0] == 67)
    {
      trace_curve();
    }
    else if (command[0] == 68)
    {
      Serial.println(current_panel);
    }
    else if (command[0] == 69)
    {
      step_decoder();
    }
    else if (command[0] == 70)
    {
      size_t bytesRead = Serial.readBytes(params, 1);
      if (0 < params[0] < 4095) Serial.println(dac.setValue(params[0]));
    }
    // TODO:  conversions from bin to voltage, curve tracing time, does the DAC make the resistor ladder obsolete, current source calibration, onewire temperature measurements,
    //        sun sensor interfacing, selection of resistor ladder resistors, reverse biased panels 
  }
}

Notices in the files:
Flight Hardware/perovskite_contact_board/V3/perovskite_contact_board.kicad_pcb:
Copyright (c) 2023
perovskite_contact_board/V3/perovskite_contact_board.sch:
Copyright (c) 2022
parts and their libraries:
Copyright 2016 Accelerated Designs. All rights reserved.
Copyright 2021 Accelerated Designs. All rights reserved.
